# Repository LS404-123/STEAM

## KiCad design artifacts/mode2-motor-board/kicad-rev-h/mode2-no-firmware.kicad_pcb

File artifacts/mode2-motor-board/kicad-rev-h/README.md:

# 模式二 H 版：指定 SS12D10G5 直腳開關

依使用者提供的商品圖更換 G 版 S0。此為打樣設計，尚未實機測試。商品標示 **2A／125V AC**，直流馬達負載能力仍未驗證。

## 本次修改

- S0：SS12D10G5 直腳，3 腳、2 檔、單刀雙擲；非 D06 彎腳款。
- 本體依商品圖為 12.7 × 6.7 × 6.3 mm，柄高 5 mm；腳距由 4.70 改為 4.80 mm。
- 接腳截面 1.3 × 0.8 mm；PCB 採 1.85 mm 成品孔、2.60 mm 焊盤。
- 更新原理圖、S0 封裝、走線、3D 外形及 BOM；R／C 數值與控制邏輯沿用 G 版。
- 一塊 40 × 40 mm PCB，兩層銅線、1.6 mm 厚、22 個零件全部裝正面；無 Q1、LED、MCU 或模式跳線。

來源：sources/S0-SS12D10G5-user.png。商品圖註明手量誤差 0.5–1 mm；量產前須以樣品或原廠圖確認腳距、插入配合及接點方向。本封裝依標稱尺寸繪製。

S0 接線：1 接 BATT+、2 接 VCC、3 接 DISCH。接通 1–2 為開機，接通 2–3 為關機並透過 R6 放電。中腳為公共端的設計假設須實測；裝配前用萬用表確認左右撥向與 ON／OFF 絲印一致。直流負載、接觸壓降及溫升待測；圖片不能證明 150 件即時庫存。

## 接線及操作

零件面朝上、S0 在左上角：

| 接口 | 接法 |
|---|---|
| P1／BAT，右上 | 上孔負極，下孔正極；只接兩粒 AA 串聯 |
| P4／MOTOR，右側 | 上孔 M2，下孔 M1；方向相反時關機後交換兩線 |
| P2／SW1，左下 | 左孔 NO，右孔 COM |
| P3／SW2，下方 | 左孔 NO，右孔 COM |

微動開關使用 COM／NO，NC 不接。C8 是板外 100nF 陶瓷電容，直接跨接 FA-130 馬達兩端，不接 GND。接線前取出電池。

放開兩個開關後開機，馬達應保持停止。每次按下後放開，一次只按一個開關。

| 目前狀態 | 按 SW1 | 按 SW2 |
|---|---|---|
| 停止 | 正轉 | 保持停止 |
| 正轉 | 保持正轉 | 反轉 |
| 反轉 | 停止 | 保持反轉 |

沒有三秒鎖定；停止後放開再按 SW1 可重新啟動。同時按兩鍵的行為未定義。

## 檔案與 3D

- exports/原理圖-H.pdf：A3 可放大原理圖；同名網絡標籤表示相連。
- exports/模式二控制板H版使用手冊.pdf：接線、操作、邏輯、走線及原理圖；不含 R／C 計算。
- exports/PCB-3D.png、PCB正面.png、PCB背面.png：原生 KiCad 算繪圖，非實物照片。
- exports/pcb-traces-front.png、pcb-traces-back.png：走線圖；背面是板背視角。
- exports/完整3D板.wrl：含模型的 VRML，單位 mm；S0 等部分模型僅表達外形。
- fabrication/：與本版 PCB 對應的 Gerber 及鑽孔檔，供原型打樣，勿混用 G 版。

解壓完整專案，用 KiCad 10 開啟 mode2-no-firmware.kicad_pro，進入 PCB 編輯器，按 **Alt＋3** 看 3D。BoardF.pretty 是沿用的庫名稱；板上版本為 MODE 2 / H。

## 裝配與檢查

物料見 BOM.csv。U3 底部散熱焊盤必須焊接，適合交貼片店處理；S0 和四組端子從正面插入、背面焊接。C4 正極朝板下方，D1 色帶端朝左。

電源／馬達主幹 1.00 mm，一般訊號 0.25 mm，WSON 短引出線 0.20 mm；DRC 間距 0.20 mm。FR-4、40 × 40 mm、兩層、1.6 mm、1oz 銅，沒有安裝孔。

結果見 verification.json 和 reports/：原理圖接腳、PCB 一致性、漏接、間距、90° 銅線轉彎及指定邏輯模型檢查。這些檢查不能驗證開關額定或取代實機測試。兩粒 AA 在負載下須維持至少 2V；沒有額外固定 0.8A 限流。

## 重建

用 KiCad Python 依次執行 build_schematic.py、build_board.py、route_board.py，先執行 DRC 產生 reports/drc.json，再執行 finish_board.py 及 export_and_check.ps1。圖像及手冊從新版匯出檔重建，檢視後執行 package.py。模型與封裝隨包附上。

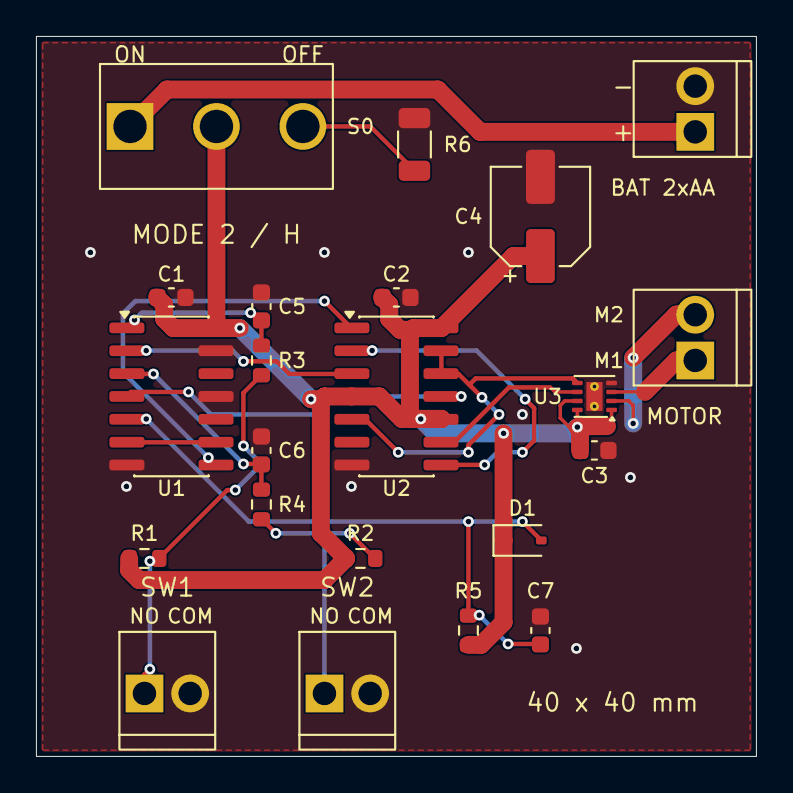
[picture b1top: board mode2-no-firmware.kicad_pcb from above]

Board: 2 copper layers, 40.0 x 40.0 mm, 22 parts (0 on the bottom side), 18 nets.

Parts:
C1, C2, C3: 100nF / 16V; C0603
C4: 100uF / 6.3V; CP5
C5, C6: 220nF; C0603
C7: 100nF; C0603
D1: BAT54WS; SOD323
P1: 電池螺絲端子; KF128_2P
P2: SW1 螺絲端子; KF128_2P
P3: SW2 螺絲端子; KF128_2P
P4: 馬達螺絲端子; KF128_2P
R1, R2, R5: 100k; R0603
R3, R4: 1k; R0603
R6: 100R / 0.25W; R1206
S0: SS12D10G5
U1: SN74HC14DR; SOIC14
U2: SN74HC74DR; SOIC14
U3: DRV8212DSGR; WSON8

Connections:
/BATT+: P1.1, S0.1
/CLK1: U1.2, U2.3
/CLK2: U1.4, U2.11
/DB1: C5.1, R3.2, U1.1
/DB2: C6.1, R4.2, U1.3
/DISCH: R6.1, S0.3
/GND: C1.2, C2.2, C3.2, C4.2, C5.2, C6.2, C7.2, P1.2, P2.2, P3.2, R6.2, U1.7, U1.11, U1.13, U2.7, U3.4, U3.9
/M1: P4.1, U3.3
/M2: P4.2, U3.2
/NOT_REV: U2.2, U2.8
/POR_INV: U1.6, U1.9
/POR_RC: C7.1, D1.2, R5.2, U1.5
/RESET_N: U1.8, U2.1
/REV: U2.9, U3.6
/RUN: U2.5, U2.12, U2.13, U3.5
/SW1: P2.1, R1.2, R3.1
/SW2: P3.1, R2.2, R4.1
/VCC: C1.1, C2.1, C3.1, C4.1, D1.1, R1.1, R2.1, R5.1, S0.2, U1.14, U2.4, U2.10, U2.14, U3.1, U3.7, U3.8

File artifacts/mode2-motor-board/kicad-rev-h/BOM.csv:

位號,數量,型號或規格,封裝,位置,備註
U1,1,SN74HC14DR,SOIC-14 3.9×8.7mm,正面,施密特反相器；買 DR 封裝版本
U2,1,SN74HC74DR,SOIC-14 3.9×8.7mm,正面,雙 D 觸發器；免燒錄
U3,1,DRV8212DSGR,WSON-8 2×2mm,正面,表面標記 212；底部焊盤必須焊接
R1/R2/R5,3,100kΩ ±1% ≥0.063W,0603 1608 metric,正面,上拉及復位
R3/R4,2,1kΩ ±1% ≥0.063W,0603 1608 metric,正面,開關消抖
R6,1,100Ω ±1% 0.25W,1206 3216 metric,正面,關機放電
C1/C2/C3,3,100nF 16V X7R ±10%,0603 1608 metric,正面,電源去耦
C4,1,EEEFK0J101UR 100µF 6.3V,直徑5mm 高5.8mm SMD,正面,有極性電解；正極朝板下方
C5/C6,2,220nF ≥10V X7R ±10%,0603 1608 metric,正面,開關消抖
C7,1,100nF ≥10V X7R ±10%,0603 1608 metric,正面,上電復位
D1,1,BAT54WS-7-F,SOD-323,正面,色帶陰極朝左；接 VCC
S0,1,SS12D10G5 直腳（使用者指定）,直插 SPDT；腳距4.80mm；孔徑1.85mm,正面,商品標示2A／125V AC；DC負載及實物腳距待驗證；非D06彎腳
P1/P2/P3/P4,4,KEFA KF128-2.54-2P C474920,直插；腳距2.54mm；孔徑1.30mm,正面,四組螺絲端子；不要買5.08mm孔距版本
C8,1,100nF ≥10V 陶瓷電容,按馬達接線空間選擇,板外,直接跨接馬達兩端；不計入22件PCB零件
S1/S2,2,帶線瞬時機械微動開關,接 COM／NO,板外,NC 不接；不計入22件PCB零件

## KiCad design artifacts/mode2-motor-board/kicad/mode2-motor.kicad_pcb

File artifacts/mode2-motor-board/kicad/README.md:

# 模式二馬達控制板 · B 版原型

KiCad 10 專案。PCB 尺寸 **22 × 20 mm**，雙面、1.6 mm FR-4、外層銅厚 1 oz；所有元件裝在正面。保留板上 S0 電源開關，沒有 LED 和模式選擇跳線。

此交付包含完整原理圖、已佈線 PCB、自含符號與封裝庫、物料表、檢查報告，以及 Gerber／鑽孔檔。**目前是硬體原型；尚未製造、焊接、燒錄或實機測試。套件不含韌體，空白 U1 不會執行模式二。**

## 開啟與檔案

1. 解壓整個專案資料夾，保留 `Mode2.pretty`、`models` 及兩個 `*-lib-table`。
2. 在 KiCad 10 開啟 `mode2-motor.kicad_pro`。
3. 開啟 `mode2-motor.kicad_sch` 查看原理圖，或 `mode2-motor.kicad_pcb` 查看板圖。
4. `exports/mode2-schematic.pdf` 是可直接閱讀的原理圖；`exports/pcb-top.png`、`pcb-bottom.png` 及 `pcb-3d.png` 是預覽。
5. `fabrication/` 及同名壓縮包提供打板資料；`BOM.csv` 是物料表。Gerber 已包含佈線和鋪銅。

`build_board.py` 是此次建檔來源，需 KiCad 的 Python／pcbnew。它會重建並覆寫設計檔；若之後在 KiCad 手動修改，請勿直接重跑它。

## 接線

| 接點 | 腳 1（方形焊盤） | 腳 2 | 腳 3 |
|---|---|---|---|
| P1 電池 | 電池正極 | 電池負極／GND | — |
| P2 SW1 | 微動開關 NO | 微動開關 COM／GND | — |
| P3 SW2 | 微動開關 NO | 微動開關 COM／GND | — |
| P4 馬達 | OUT1 | OUT2 | — |
| P5 燒錄 | VBAT／目標電壓 | UPDI | GND |

- **使用 2 粒 AA 串聯。不要接 3 粒 AA、USB 5 V 或 9 V 電池。** 2 粒鎳氫電池標稱 2.4 V，2 粒鹼性電池標稱 3 V。馬達端電壓會隨電池狀態及負載變化。
- P1、P4 是間距 2.5 mm、孔徑 0.8 mm 的焊線孔。P5 間距 2.54 mm、孔徑 1.0 mm，可裝 1×3 排針，或直接接燒錄線。
- P2、P3 改用 **JST PH 2.0 mm 白色兩針直立插座 B2B-PH-K-S(LF)(SN)**，配套插頭是 **PHR-2**。可購買已壓好端子的 PH 2.0 mm 兩芯線組，每個開關一組；不要買成 XH 2.5 mm。
- SW1／SW2 只使用 COM、NO；NC 不接。線組接 P2/P3 的 1 腳至 NO、2 腳至 COM；依腳號核對，不能只靠線的顏色判斷。S1/S2 是板外微動開關。
- C4 是 **100 nF 無極性陶瓷電容**，直接焊在馬達兩端，不裝在這片 PCB。馬達兩端均不可固定接 GND。
- S0 型號固定為 **E-Switch 500ASSP1M2QE**。2 腳為共用端，1–2 接通時開機；切換至 2–3 時關機，3 腳不接其他網路。
- C3 的正極接 VBAT，負極接 GND；依 PCB 的「+」與電容本體負極標記核對方向。U1/U2 依封裝的 1 腳標記安裝。
- 燒錄使用支援 ATtiny202 的 UPDI 工具。燒錄器和電池只能選一個供電來源；若由電池供電，燒錄器的 Vtarget 接腳須作電壓感測，不能同時輸出另一個電壓。

## 元件與選型依據

板上共 9 個必要元件：2 顆 IC、1 顆電阻、3 顆電容、1 個電源開關及 2 個白色插座。另需兩組配套插頭線組；P1、P4 的焊線孔和 P5 燒錄孔無需另購連接器。

| 位號 | 型號／規格 | 封裝與說明 |
|---|---|---|
| U1 | Microchip ATtiny202-SSNR | SOIC-8，3.9 × 4.9 mm，腳距 1.27 mm；須燒錄 |
| U2 | Texas Instruments DRV8213DSGR | DSG WSON-8，2 × 2 mm，腳距 0.5 mm；底部 EP 接地 |
| R1 | 1.24 kΩ，1%，≥0.063 W | 0603／1608 metric；例如 Yageo RC0603FR-071K24L |
| C1、C2 | 100 nF，16 V，X7R，±10% | 0603／1608 metric；例如 Murata GRM188R71C104KA01D |
| C3 | Panasonic EEEFK0J101UR，100 µF／6.3 V | 有極性鋁電解，直徑 5 mm、高 5.8 mm；原型初值 |
| S0 | E-Switch 500ASSP1M2QE | 3 A／28 VDC 銀接點版本，直插、3 腳距 2.54 mm |
| P2、P3 | JST B2B-PH-K-S(LF)(SN) | 白色兩針直立插座，腳距 2.0 mm，本體 5.9 × 4.5 mm |
| 插頭線組（板外） | PHR-2 配套端子及兩芯線，各 2 組 | 建議直接買已壓接線組；PCB 1 腳接 NO，2 腳接 COM |
| C4（板外） | 100 nF 無極性陶瓷，耐壓 ≥10 V | 焊在馬達接點，封裝依實際焊接空間選擇 |

不要按外觀用其他三腳開關替代 S0：腳距、額定電流及本體尺寸可能不同。電容 C3 的焊盤也以這個尺寸設計，替代品需核對底座與端子。

B 版只更改 SW1/SW2 連接器、相關佈線及 P5 位置，PCB 維持 22 × 20 mm。插座及配套插頭尺寸依 [JST PH 原廠資料表](https://www.jst-mfg.com/product/pdf/eng/ePH.pdf)；直立插座從板面上方插拔。

U2 的 GAINSEL 接地，電流鏡比例為 205 µA/A，DSG 內部參考電壓標稱 0.510 V。因此 R1 的標稱限流值為 `0.510 / (205e-6 × 1240) ≈ 2.006 A`；IC 與電阻誤差會影響實際值。這是待測的啟動／負載限流設定，不是連續工作電流保證，也不是堵轉自動停機功能。[TI DRV8213 資料表](https://www.ti.com/lit/ds/symlink/drv8213.pdf)

Tamiya 980112M 的產品規格列出 1.5–3 V 工作範圍及 3 V 時 2.1 A 堵轉電流，所以本版採用 2 粒 AA。[馬達產品規格](https://www.pololu.com/product/77/specs)

U1 接腳依 [Microchip ATtiny202 資料表](https://ww1.microchip.com/downloads/aemDocuments/documents/MCU08/ProductDocuments/DataSheets/ATtiny202-204-402-404-406-DataSheet-DS40002318A.pdf)；S0 電氣及機械規格依 [E-Switch 產品頁](https://www.e-switch.com/product/500a-series-subminiature-slide-switch/) 與 [原廠尺寸圖](https://configured-product-images.s3.amazonaws.com/2D/specs/500ASSP1M2QE.pdf)；C3 尺寸依 [Panasonic 產品頁](https://industrial.panasonic.com/ww/products/pt/aluminum-cap-smd/models/EEEFK0J101UR)。

## 韌體要求（尚未實作）

| 功能 | U1 腳位 |
|---|---|
| SW1 輸入、啟用內置上拉 | 腳 2，PA6 |
| SW2 輸入、啟用內置上拉 | 腳 3，PA7 |
| U2 IN1 控制 | 腳 4，PA1 |
| U2 IN2 控制 | 腳 5，PA2 |
| UPDI 燒錄 | 腳 6，PA0 |
| IPROPI 電流感測 | 腳 7，PA3／ADC |

時鐘設定須符合電池電壓下的規格（本版以不高於 5 MHz 為目標）。開機先設定 IN1=0、IN2=0。SW1 按下後正轉（10），SW2 按下後反轉（01），再次 SW1 按下後停止（00），忽略兩個開關 3 秒，再回到等待。

00 是自由滑行停止，並非電氣煞車。按住開關不應重複觸發；需要去彈跳與按下事件判斷。其他按鍵次序、同時按下、反轉前的過渡時間、堵轉停止條件和低電壓復位策略，須在韌體階段定義並按機械負載測試。

## 製造與驗證範圍

- 雙面 FR-4、1.6 mm、1 oz。設計最小銅間距 0.15 mm；一般訊號線 0.20–0.25 mm，電池主幹 0.8 mm、馬達主幹 0.6 mm，IC 焊盤附近有短段 0.2 mm 引出線。
- U2 EP 下有兩個 0.2 mm 鍍通散熱孔，與正反面地平面連接。其他貫孔為 0.3 mm。下單時確認工廠支援 0.2 mm 鑽孔；散熱孔底面蓋油，EP 正面需焊接。裝配廠需注意小孔吸錫及 EP 焊接品質。
- U2 是底部接點 WSON，需合適的回流焊／熱風工藝；焊接 EP 是必要步驟。元件高度最高由 S0 決定，板面小並不代表總高度只有 1.6 mm。
- 板上未加入反接保護；接電池前核對 P1 極性。C3 的容量、電源尖峰、反轉電流與持續負載溫升尚待示波器及實機測試。不要用長時間堵轉來驗證功能。
- KiCad 的 ERC、DRC、未接線及原理圖一致性結果見 `reports/`；這些檢查能發現連線／幾何問題，不能代替韌體和實體測試。
- 3D 預覽使用廠方 S0 模型與 KiCad 通用元件模型；U2 是依封裝尺寸製作的外形示意。3D 圖不作外殼精密干涉檢查依據。

## 檔案來源

SOIC、WSON、電阻、電容及 JST PH 插座焊盤沿用 KiCad 10 官方封裝庫；S0 焊盤依廠方 T551002 rev G 圖面建立。KiCad 庫資產的授權資訊見 [KiCad Libraries License](https://www.kicad.org/libraries/license/)。廠方 PDF 與 STEP 原始資料保留原有權利聲明。

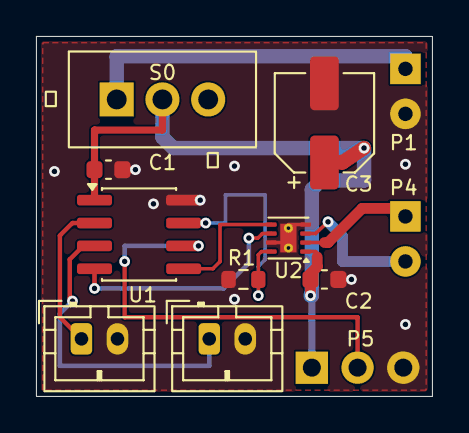
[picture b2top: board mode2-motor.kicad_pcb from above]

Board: 2 copper layers, 22.0 x 20.0 mm, 12 parts (0 on the bottom side), 11 nets.

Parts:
C1, C2: 100nF 16V; C0603
C3: 100uF 6.3V; CP5
P1: 電池 2xAA; Wire2
P2: SW1 PH-2 插座; PH2
P3: SW2 PH-2 插座; PH2
P4: 馬達接線; Wire2
P5: UPDI 燒錄; Prog3
R1: 1.24k 1%; R0603
S0: 500ASSP1M2QE; S0_500ASSP1M2QE
U1: ATtiny202-SSNR; SOIC8
U2: DRV8213DSGR; WSON8

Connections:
/BATT+: P1.1, S0.1
/GND: C1.2, C2.2, C3.2, P1.2, P2.2, P3.2, P5.3, R1.2, U1.8, U2.4, U2.7, U2.9
/IN1: U1.4, U2.6
/IN2: U1.5, U2.5
/ISENSE: R1.1, U1.7, U2.8
/OUT1: P4.1, U2.2
/OUT2: P4.2, U2.3
/SW1: P2.1, U1.2
/SW2: P3.1, U1.3
/UPDI: P5.2, U1.6
/VBAT: C1.1, C2.1, C3.1, P5.1, S0.2, U1.1, U2.1

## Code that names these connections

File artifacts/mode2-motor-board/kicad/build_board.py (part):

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defs['MCU']=sym('MCU',rect(12.7,12.7),[
 pin('1','VDD',0,15.24,270,'power_in'),pin('8','GND',0,-15.24,90,'power_in'),
 pin('2','PA6 / SW1',-15.24,5.08,0,'input'),pin('3','PA7 / SW2',-15.24,0,0,'input'),
 pin('6','PA0 / UPDI',-15.24,-7.62,0,'bidirectional'),pin('4','PA1 / IN1',15.24,5.08,180,'output'),
 pin('5','PA2 / IN2',15.24,0,180,'output'),pin('7','PA3 / ADC',15.24,-7.62,180,'input')])
defs['Driver']=sym('Driver',rect(10.16,12.7),[
 pin('1','VM',0,15.24,270,'power_in'),pin('4','GND',0,-15.24,90,'power_in'),pin('9','EP',5.08,-15.24,90,'power_in'),
 pin('6','IN1',-12.7,5.08,0,'input'),pin('5','IN2',-12.7,0,0,'input'),pin('8','IPROPI',-12.7,-7.62,0,'output'),
 pin('2','OUT1',12.7,5.08,180,'output'),pin('3','OUT2',12.7,0,180,'output'),pin('7','GAINSEL',12.7,-7.62,180,'input')])
defs['R']=sym('R',rect(1.016,2.54),[pin('1','~',0,5.08,270),pin('2','~',0,-5.08,90)],'R')
cg=poly([(-2.54,.762),(2.54,.762)])+poly([(-2.54,-.762),(2.54,-.762)])+poly([(0,2.54),(0,.762)])+poly([(0,-2.54),(0,-.762)])
defs['C']=sym('C',cg,[pin('1','~',0,5.08,270),pin('2','~',0,-5.08,90)],'C')
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stub('GND',187.96,96.52,dy=10.16)
for net,y in [('IN1',76.2),('IN2',81.28)]:
    wire((121.92,y),(170.18,y));label(net,139.7,y)
wire((121.92,88.9),(152.4,88.9));wire((152.4,88.9),(170.18,88.9));label('ISENSE',137.16,88.9);dot(152.4,88.9)
place('R1','R',152.4,106.68,prop=(162,105.41,162,107.95));wire((152.4,88.9),(152.4,101.6));stub('GND',152.4,111.76,dy=5.08)
stub('GND',195.58,88.9,dx=10.16,dy=0)
note('GAINSEL、EP（9 腳）接地。\n限流約 2 A（原型初值）。',165.1,114.3,1.15)
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    stub(net,43.18,y-2.54,dx=12.7,dy=0);stub('GND',43.18,y+2.54,dx=12.7,dy=0)
note('PH 2.0 mm 兩針插座，配 PHR-2 插頭。\n只接 COM、NO；NC 不接。\nU1 啟用內置上拉及軟件去彈跳。',20.32,113.03,1.15)
place('P4','Conn2L',228.6,78.74,prop=(231.14,68.58,231.14,71.12))
for net,y in [('OUT1',76.2),('OUT2',81.28)]:wire((195.58,y),(223.52,y));label(net,208.28,y)
place('P5','Conn3',93.98,124.46,prop=(83.82,123.19,83.82,125.73))
for net,y in [('VBAT',119.38),('UPDI',124.46),('GND',129.54)]:stub(net,99.06,y,dx=10.16,dy=0)
note('P5：焊孔間距 2.54 mm。燒錄時只用一個供電來源。',119.38,127.0,1.15)
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
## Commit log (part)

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2026-03-12 Rename grid_LED_designer.html to index.html
2026-03-12 update programme
2026-03-12 update prpgram
2026-03-15 feat: Implement dynamic grid sizing and add modal tabs for filtering sample patterns by color group.
2026-04-09 change the index.html to 3*3 LED board animation
2026-04-10 update a new LED arrangement in 5*5
2026-04-10 update color of current and some bug
